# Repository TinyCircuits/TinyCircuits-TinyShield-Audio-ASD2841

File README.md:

# TinyCircuits TinyShield Audio Board
# ASD2841 Rev5

The design files are locate under design_files/ for the TinyCircuits ASD2841 Rev 4 PCB.  This is a TinyShield board (20mm x 27.14mm) that has audio circuit and a headset connector.

Format is in Cadsoft Eagle format - Eagle version 6.2 was used for the original design.

For more infomation on this, check out the product page at TinyCircuits.com:  https://tinycircuits.com/collections/audio/products/audio-tinyshield

# License:

Design by TinyCircuits.
All design files are released under the Creative Commons Attribution Share-Alike 3.0 License, see the following link for details: http://creativecommons.org/licenses/by-sa/3.0

All text above must be included in any redistribution or derived design

This project uses designs and concepts developed as part of the Arduino project and the LilyPad project.  The TinyCircuits design files themselves (schematics, PCB and libraries) are not directly derived from these works' design files and have been created new, however the concepts and basic architecture behind the TinyDuino and TinyLily products are derived and we thank the hard work of the organizations below for their contributions to open-source hardware:
  
Original Arduino Uno Design by Team Arduino

LilyPad Arduino Design by Leah Buechley and Sparkfun Electronics

Please support the open-source hardware community

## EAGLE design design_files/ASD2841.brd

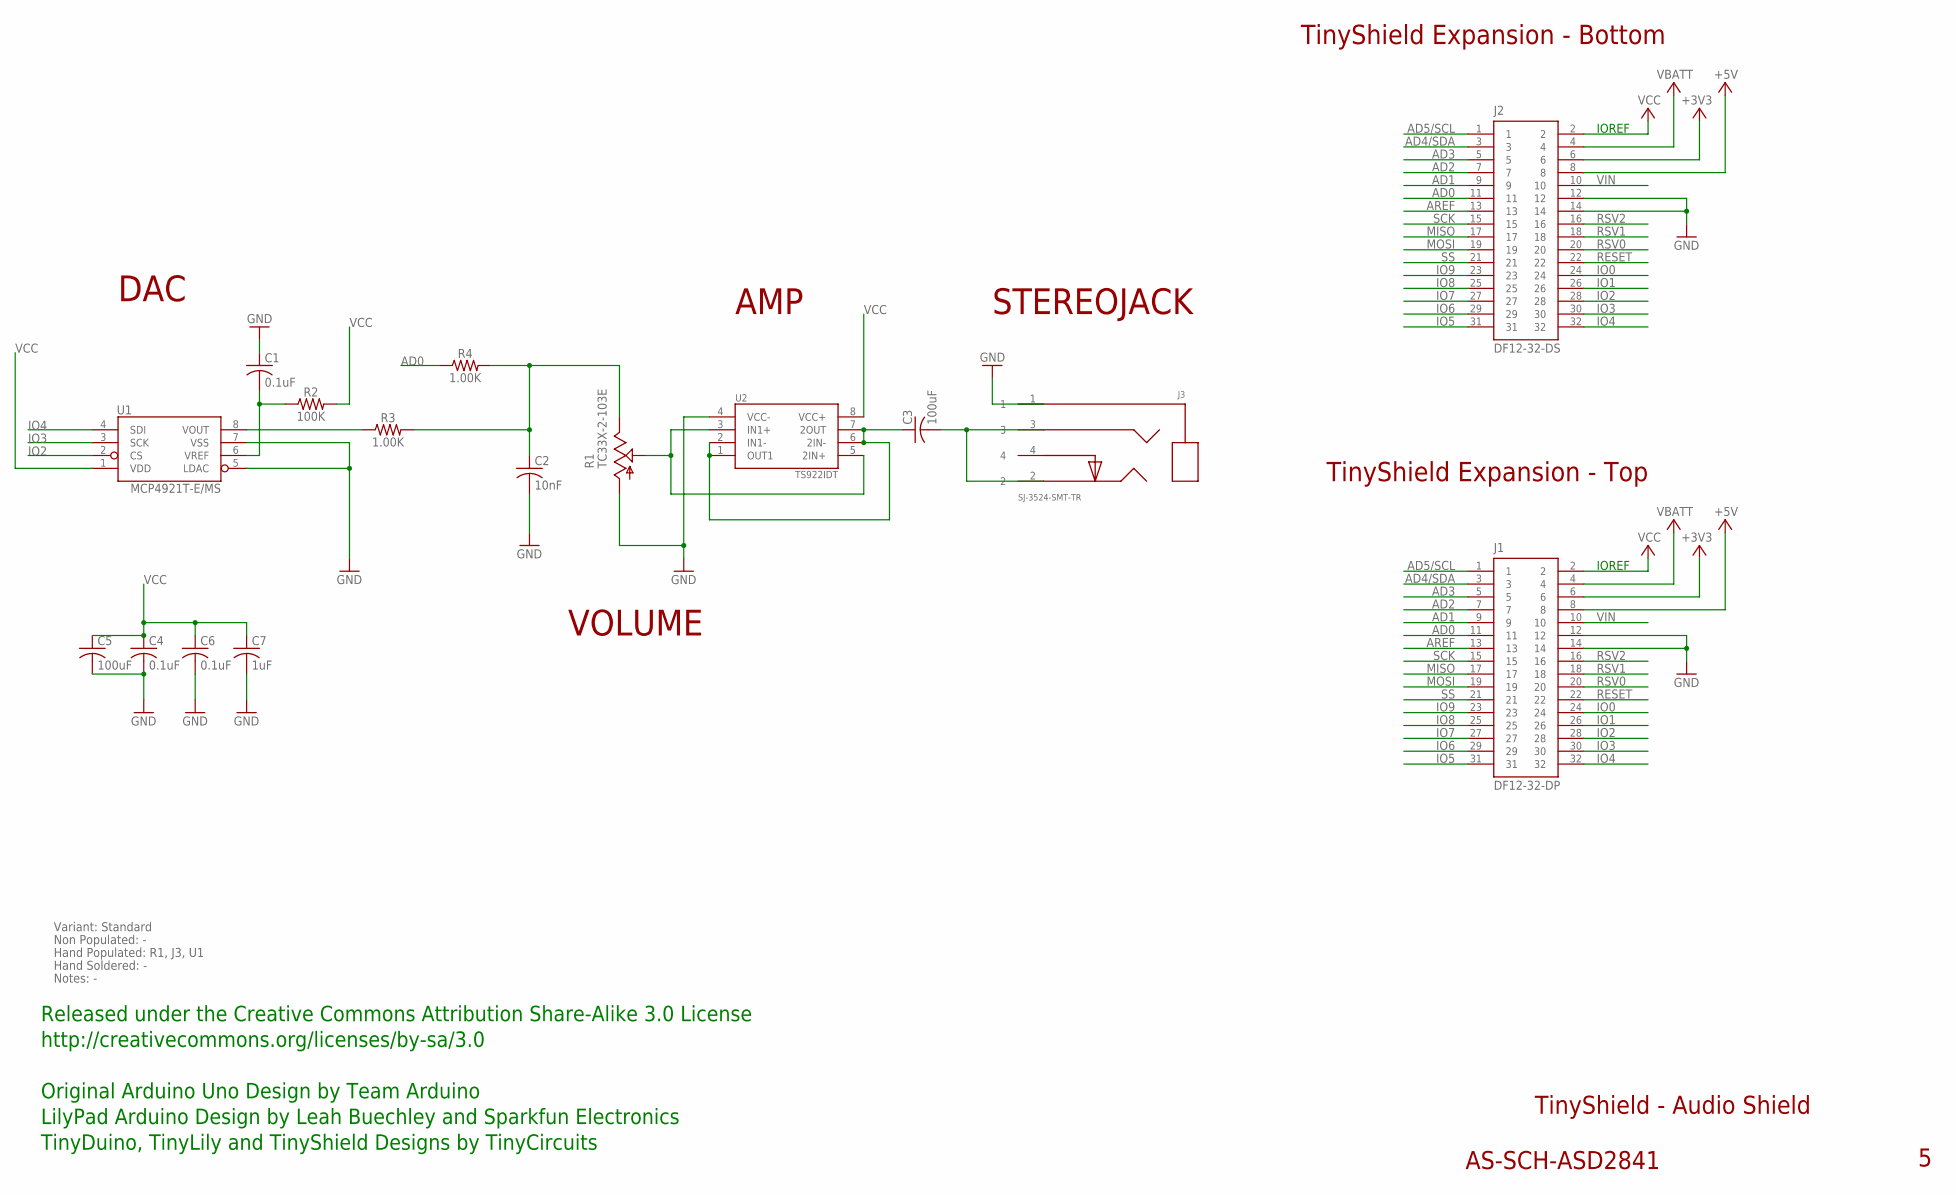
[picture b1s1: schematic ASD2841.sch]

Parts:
C1, C4: 0.1uF; C0402
C2: 10nF; C0402
C3, C5: 100uF; C1206
C6: 0.1uF; C0402; PARTNO AS-ITM-00008
C7: 1uF; C0402; PARTNO AS-ITM-00105
J1: DF12-32-DP; PARTNO AS-ITM-00015
J2: DF12-32-DS; PARTNO AS-ITM-00012
J3: SJ-3524-SMT-TR
R1: TC33X-2-103E; TC33X-2-104E
R2: 100K; 0402
R3, R4: 1.00K; 0402
U1: MCP4921T-E/MS; MSOP8
U2: TS922IDT; SO-08

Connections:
+3V3: J1.6, J2.6
+5V: J1.8, J2.8
AD0: J1.11, J2.11, R4.1
AD1: J1.9, J2.9
AD2: J1.7, J2.7
AD3: J1.5, J2.5
AD4/SDA: J1.3, J2.3
AD5/SCL: J1.1, J2.1
AREF: J1.13, J2.13
GND: C1.1, C2.2, C4.2, C5.2, C6.2, C7.2, J1.12, J1.14, J2.12, J2.14, J3.1, R1.1 (A), U1.5 (LDAC), U1.7 (VSS), U2.4 (VCC-)
IO0: J1.24, J2.24
IO1: J1.26, J2.26
IO2: J1.28, J2.28, U1.2 (CS)
IO3: J1.30, J2.30, U1.3 (SCK)
IO4: J1.32, J2.32, U1.4 (SDI)
IO5: J1.31, J2.31
IO6: J1.29, J2.29
IO7: J1.27, J2.27
IO8: J1.25, J2.25
IO9: J1.23, J2.23
MISO: J1.17, J2.17
MOSI: J1.19, J2.19
unnamed: R1.2 (S), U2.3 (IN1+), U2.5 (2IN+)
unnamed: C3.1, U2.1 (OUT1), U2.2 (IN1-), U2.6 (2IN-), U2.7 (2OUT)
unnamed: C1.2, R2.1, U1.6 (VREF)
unnamed: R3.1, U1.8 (VOUT)
unnamed: C2.1, R1.3 (E), R3.2, R4.2
unnamed: C3.2, J3.2, J3.3
RESET: J1.22, J2.22
RSV0: J1.20, J2.20
RSV1: J1.18, J2.18
RSV2: J1.16, J2.16
SCK: J1.15, J2.15
SS: J1.21, J2.21
VBATT: J1.4, J2.4
VCC: C4.1, C5.1, C6.1, C7.1, J1.2, J2.2, R2.2, U1.1 (VDD), U2.8 (VCC+)
VIN: J1.10, J2.10

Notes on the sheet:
TinyShield Expansion - Bottom
TinyShield - Audio Shield
AS-SCH-ASD2841
TinyShield Expansion - Top
IOREF
Released under the Creative Commons Attribution Share-Alike 3.0 License
http://creativecommons.org/licenses/by-sa/3.0
LilyPad Arduino Design by Leah Buechley and Sparkfun Electronics
TinyDuino, TinyLily and TinyShield Designs by TinyCircuits
Original Arduino Uno Design by Team Arduino
DAC
AMP
STEREOJACK
VOLUME
Non Populated: -
Hand Populated: R1, J3, U1
Hand Soldered: -
Variant: Standard
Notes: -

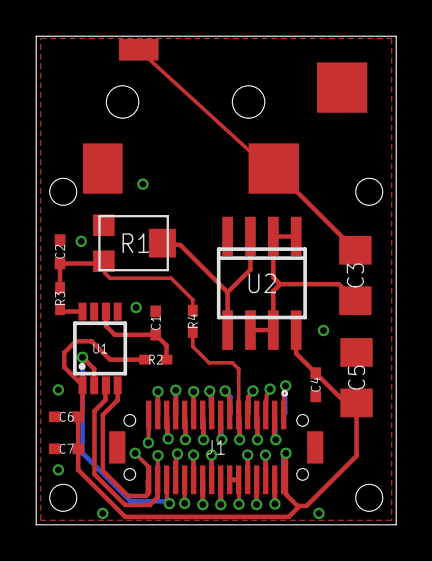
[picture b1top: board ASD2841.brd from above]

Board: 2 copper layers, 20.0 x 27.1 mm, 17 parts (1 on the bottom side), 37 nets.

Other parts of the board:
U$1: DOCFIELD-TINYCIRCUITS-PCB

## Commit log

2019-01-04 update format
2019-05-22 added images
2019-05-23 updated images
2020-02-11 image update
2020-07-28 Add CAD data
2020-08-14 Update CAD drawing
